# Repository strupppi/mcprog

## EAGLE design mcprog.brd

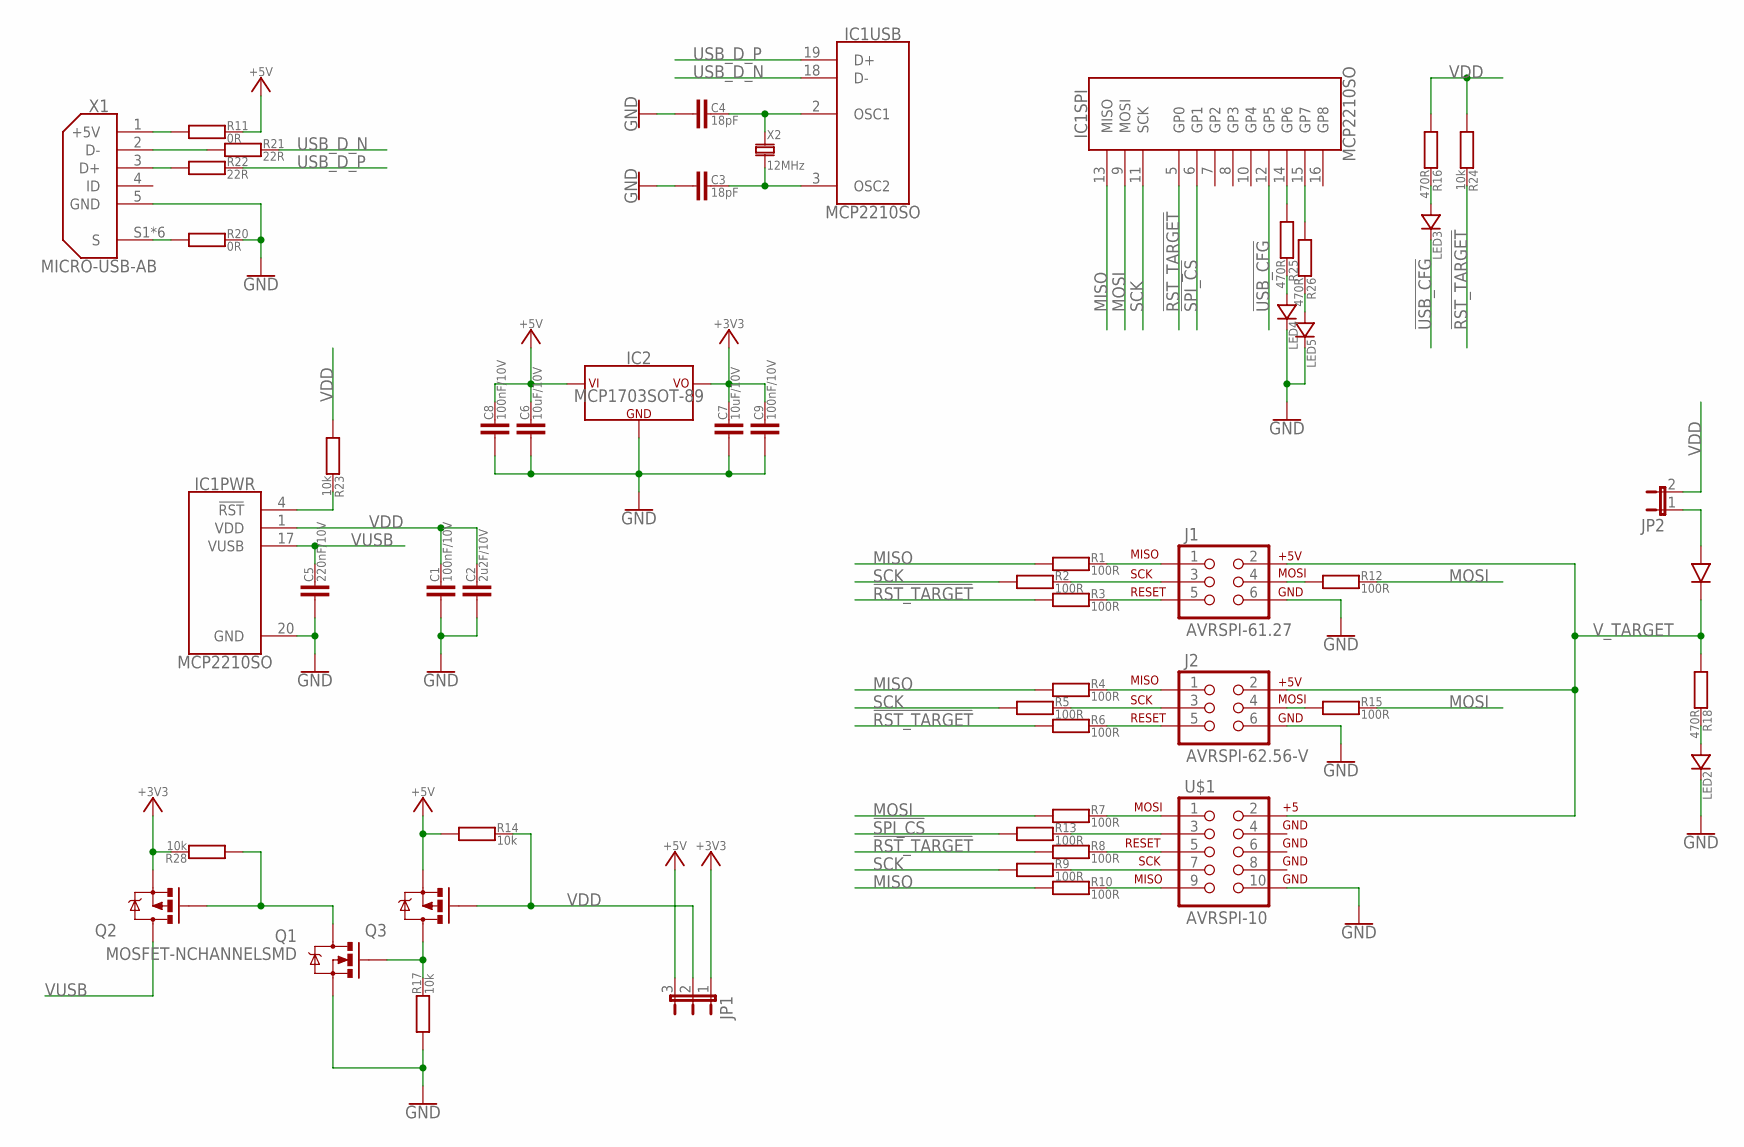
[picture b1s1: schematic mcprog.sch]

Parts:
C1, C8, C9: 100nF/10V; C0603
C2: 2u2F/10V; C1206
C3, C4: 18pF; C0603
C5: 220nF/10V; C0603
C6, C7: 10uF/10V; C1206
D1: 1N5819HW; SOD123
IC1: MCP2210SO; SOIC20-W
IC2: MCP1703SOT-89; SOT89
J1: AVRSPI-61.27; 2X3-1.27
J2: AVRSPI-62.56-V; 2X3-NS
JP1: JP2E; JP2
JP2: JP1E; JP1
LED2, LED3, LED4, LED5: LED0603
Q1: MOSFET-NCHANNELSMD; SOT23-3
Q2, Q3: MOSFET-PCHANNEL; SOT23
R1, R2, R3, R4, R5, R6, R7, R8, R9, R10, R12, R13, R15: 100R; R0603
R11, R20: 0R; R0603
R14, R17, R23, R24, R28: 10k; R0603
R16, R18, R25, R26: 470R; R0603
R21, R22: 22R; R0603
U$1: AVRSPI-10; AVR_ICSP
X1: MICRO-USB-AB; ZX62-B-5PA(11)
X2: 12MHz; HC49UP

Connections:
!RST_TARGET!: IC1.5 (GP0), R3.1, R6.1, R8.1, R24.2
!SPI_CS!: IC1.6 (GP1), R13.1
!USB_CFG!: IC1.12 (GP5), LED3.C
+3V3: C7.2, C9.2, IC2.3 (VCC), JP1.1, Q2.2 (S), R28.2
+5V: C6.2, C8.2, IC2.2 (VIN), IC2.4 (VIN), JP1.3, Q3.2 (S), R11.2, R14.1
GND: C1.1, C2.1, C3.1, C4.1, C5.1, C6.1, C7.1, C8.1, C9.1, IC1.20 (GND), IC2.1 (GND), J1.6 (GND), J2.6 (GND), LED2.C, LED4.C, LED5.C, Q1.2 (S), R17.1, R20.2, U$1.10, X1.5 (GND)
MISO: IC1.13 (MISO), R1.1, R4.1, R10.1
MOSI: IC1.9 (MOSI), R7.1, R12.2, R15.2
unnamed: J1.1 (MISO), R1.2
unnamed: J1.3 (SCK), R2.2
unnamed: J1.5 (RESET), R3.2
unnamed: J2.1 (MISO), R4.2
unnamed: J2.3 (SCK), R5.2
unnamed: J2.5 (RESET), R6.2
unnamed: R7.2, U$1.1
unnamed: R8.2, U$1.5
unnamed: R9.2, U$1.7
unnamed: R10.2, U$1.9
unnamed: Q1.1 (G), Q3.3 (D), R17.2
unnamed: LED3.A, R16.2
unnamed: Q1.3 (D), Q2.1 (G), R28.1
unnamed: J2.4 (MOSI), R15.1
unnamed: LED2.A, R18.2
unnamed: IC1.14 (GP6), R25.1
unnamed: J1.4 (MOSI), R12.1
unnamed: R13.2, U$1.3
unnamed: C4.2, IC1.2 (OSC1), X2.1
unnamed: C3.2, IC1.3 (OSC2), X2.2
unnamed: R21.1, X1.2 (D-)
unnamed: R22.1, X1.3 (D+)
unnamed: R11.1, X1.1 (+5V)
unnamed: R20.1, X1.S1 (S), X1.S2 (S), X1.S3 (S), X1.S4 (S), X1.S5 (S), X1.S6 (S)
unnamed: LED4.A, R25.2
unnamed: D1.A, JP2.1
unnamed: IC1.4 (!RST!), R23.2
unnamed: LED5.A, R26.2
unnamed: IC1.15 (GP7), R26.1
SCK: IC1.11 (SCK), R2.1, R5.1, R9.1
USB_D_N: IC1.18 (D-), R21.2
USB_D_P: IC1.19 (D+), R22.2
VDD: C1.2, C2.2, IC1.1 (VDD), JP1.2, JP2.2, Q3.1 (G), R14.2, R16.1, R23.1, R24.1
VUSB: C5.2, IC1.17 (VUSB), Q2.3 (D)
V_TARGET: D1.C, J1.2 (+5V), J2.2 (+5V), R18.1, U$1.2

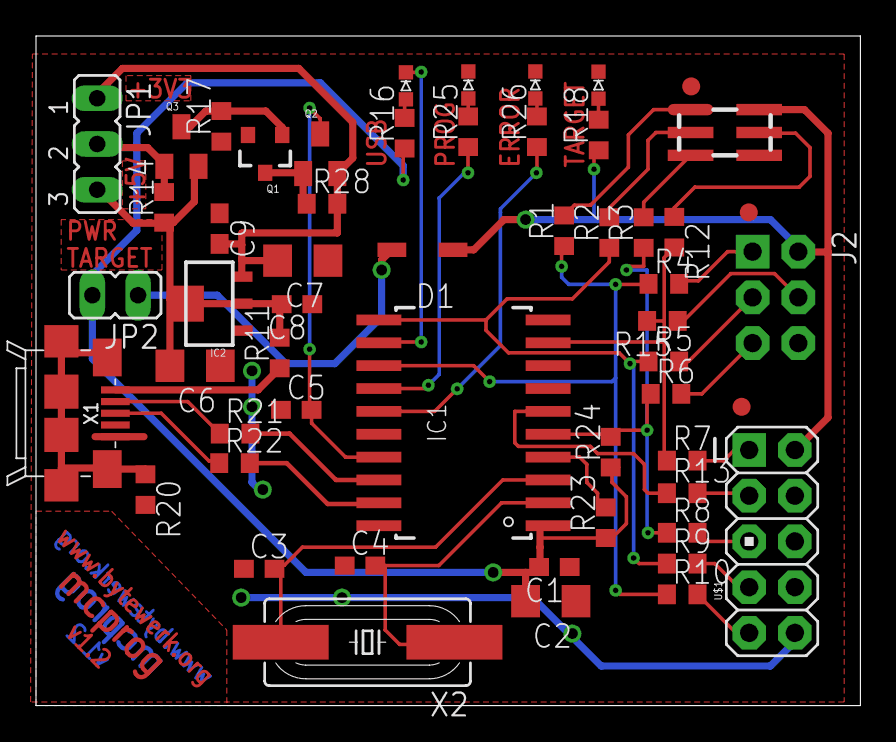
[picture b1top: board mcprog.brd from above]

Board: 2 copper layers, 45.8 x 37.2 mm, 52 parts (0 on the bottom side), 43 nets.

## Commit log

2014-09-13 schematics: done.
2014-09-13 board, v1
2014-09-14 v1.0
2014-09-14 Fixing some minor DRC problems. R23 now is 10k
2014-09-14 improve GND path
2014-09-14 put flipped text on backside
2014-10-12 attach PROG led to GPIO6 instead of GPIO8 GPIO8 refused to be an output for some unknown reason
2014-10-20 v1.2 with various small changes
2016-05-17 removed hgignore file

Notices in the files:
parts and their libraries:
bytewerk-con: Creative Commons 3.0 CC-BY-SA
bytewerk-crystal: CC-BY-SA
mcp2210: Creative Commons v3.0 CC-BY-SA
